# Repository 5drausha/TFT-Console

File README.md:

# TFT-Console
A small console with 6 buttons and a 2.8" touch screen, powered with a raspberry pi pico.

This is my project for the Displays week. It is a small game console, with 6 Cherry MX switches as controls, a Raspberry Pi Pico to control the display, and a 2.8 inch TFT touch screen. 
I wanted this to be more than just a game console. It's going to have a few apps like drawing, games, and other utilities like a stopwatch or a clock.
Unfortunately, I wasn't able to find a 3D model for the screen, which is why I only have a render of the PCB.

****PCB and Schematic****

Below are the PCB and the Schematic. I had to learn a lot about TFT screens and how to wire them up to make these. I wanted to make the board as compact as possible, and to save money on PCB costs as the price gets higher if a side is more than 100mm long. Because of this, I decided to put the raspberry pi pico on the back, behind the screen. For the PCB, the only warnings I had were silkscreen clipped errors, which can be ignored.

This is the schematic. At first I had a bunch of errors because I tried to connect 2 labels to the same pin, but then I realized I had to combine both pins into one, and I got 0 errors.

**Firmware**

For the firmware, I didn't make the whole console with apps and stuff yet, cuz it's hard to test if parts of the code work, and I don't want to accidentally build on something that won't work. For that reason, I made a placeholder code that displays six different colored counters on the screen that is tied to a respective one of my Cherry MX switches, and when each button is pressed, its counter goes up. Its a simple code, and doesn't do much, but its not a bad start and it'll be good for testing my screen and buttons.

**BOM**

I bought my main parts on Aliexpress and the PCB on JLCPCB. The raspberry pi pico was very cheap, coming to only $1.55. The TFT on the other hand, wasn't so cheap, coming to $10.44, which is understandable being the main component of the project. The PCB costed $4, and $1.50 for shipping. For the Cherry MX switches, I'm going to be using some of the leftover switches from my previous project the MIDI keypad to save money. That brings the total to $19.29, althouhg prices are subject to change.

Well, this project was really fun, and I learnt so much from it. I got into the new territory of screens and displays, and its the first time I've used python to code instead of C++. I also learned new things in Kicad, even though I used it for a few other projects. This week was lovely, and I'm happy and thankful that half-life was able to give me this opportunity. Thank you!

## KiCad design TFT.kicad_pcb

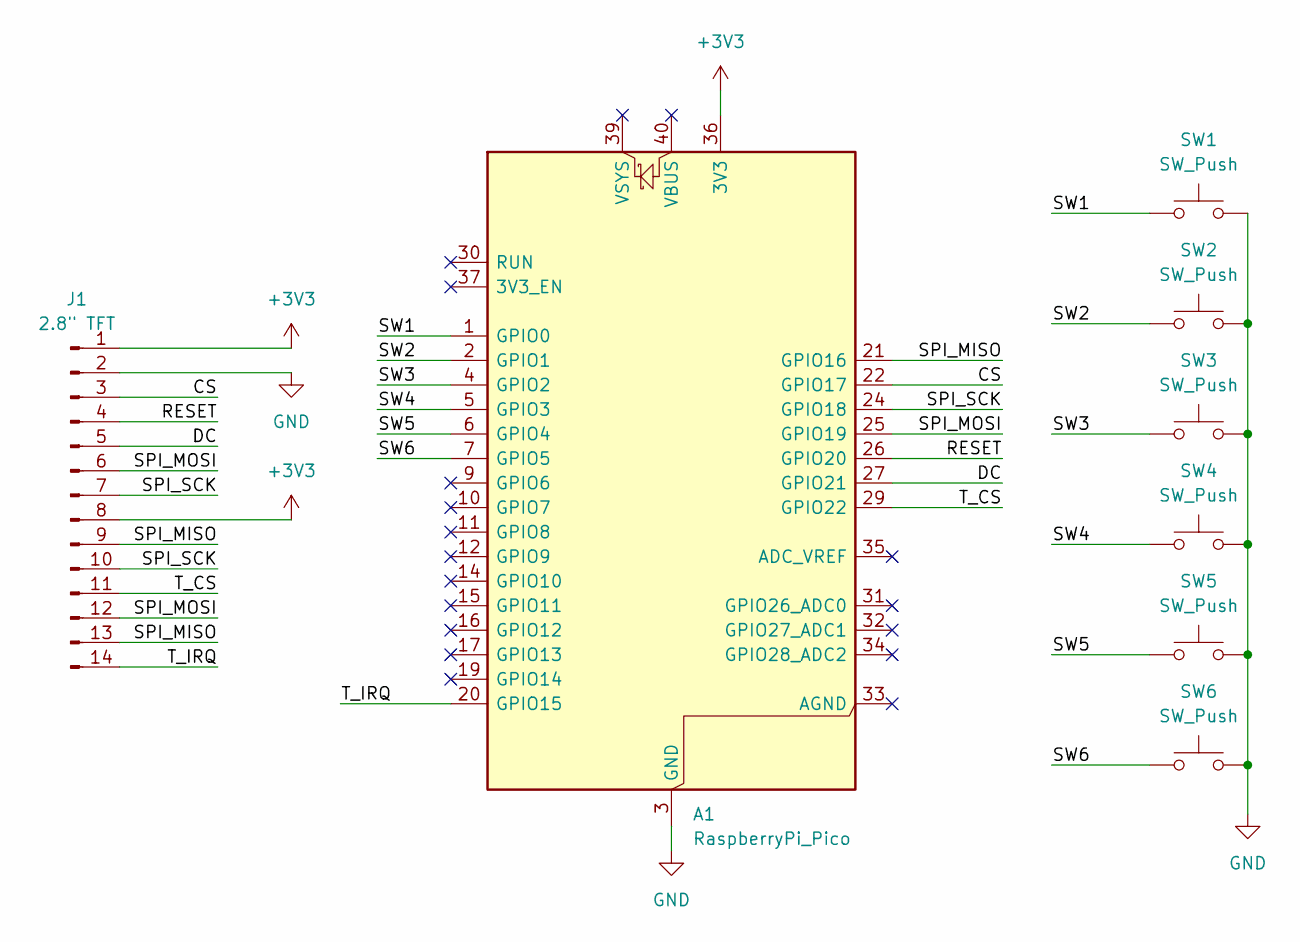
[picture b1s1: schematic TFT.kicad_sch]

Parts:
A1: RaspberryPi_Pico; RaspberryPi_Pico_Common_Unspecified
J1: 2.8" TFT; PinSocket_1x14_P2.54mm_Vertical
SW1, SW2, SW3, SW4, SW5, SW6: SW_Push; SW_Cherry_MX_1.00u_PCB

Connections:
+3V3: A1.36 (3V3), J1.1, J1.8
/CS: A1.22 (GPIO17), J1.3
/DC: A1.27 (GPIO21), J1.5
/RESET: A1.26 (GPIO20), J1.4
/SPI_MISO: A1.21 (GPIO16), J1.9, J1.13
/SPI_MOSI: A1.25 (GPIO19), J1.6, J1.12
/SPI_SCK: A1.24 (GPIO18), J1.7, J1.10
/SW1: A1.1 (GPIO0), SW1.1
/SW2: A1.2 (GPIO1), SW2.1
/SW3: A1.4 (GPIO2), SW3.1
/SW4: A1.5 (GPIO3), SW4.1
/SW5: A1.6 (GPIO4), SW5.1
/SW6: A1.7 (GPIO5), SW6.1
/T_CS: A1.29 (GPIO22), J1.11
/T_IRQ: A1.20 (GPIO15), J1.14
GND: A1.3 (GND), A1.8 (GND), A1.13 (GND), A1.18 (GND), A1.23 (GND), A1.28 (GND), A1.38 (GND), J1.2, SW1.2, SW2.2, SW3.2, SW4.2, SW5.2, SW6.2

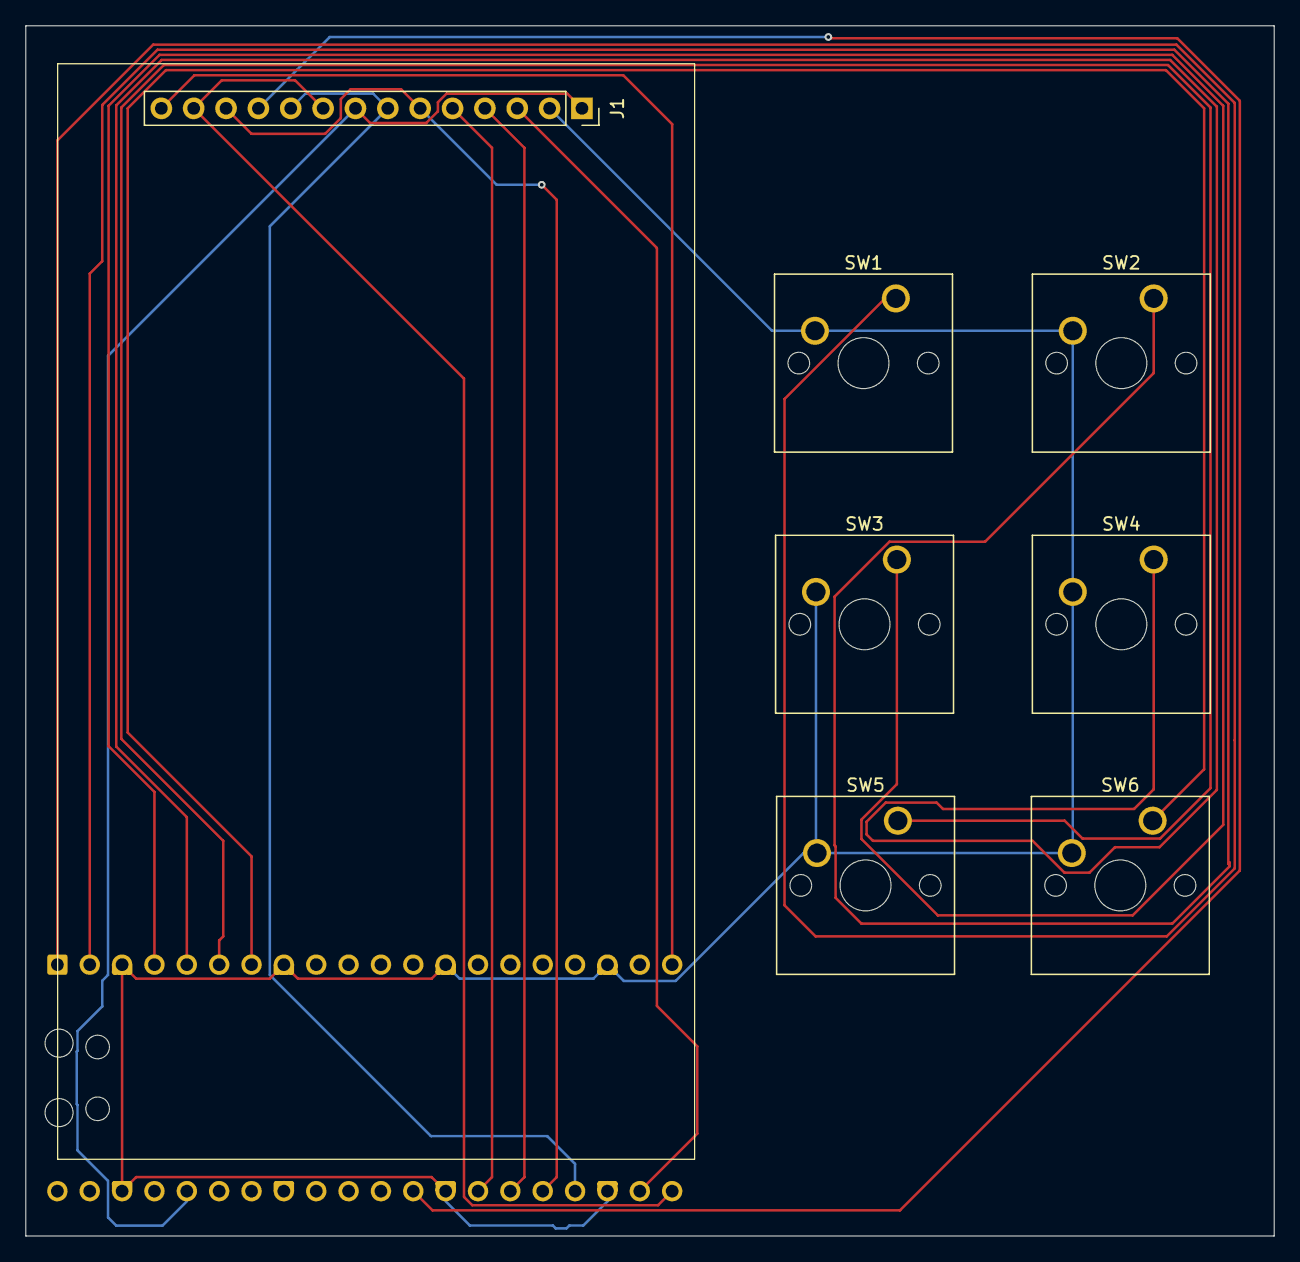
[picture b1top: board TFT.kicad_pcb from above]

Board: 2 copper layers, 98.0 x 95.0 mm, 8 parts (1 on the bottom side), 16 nets.
